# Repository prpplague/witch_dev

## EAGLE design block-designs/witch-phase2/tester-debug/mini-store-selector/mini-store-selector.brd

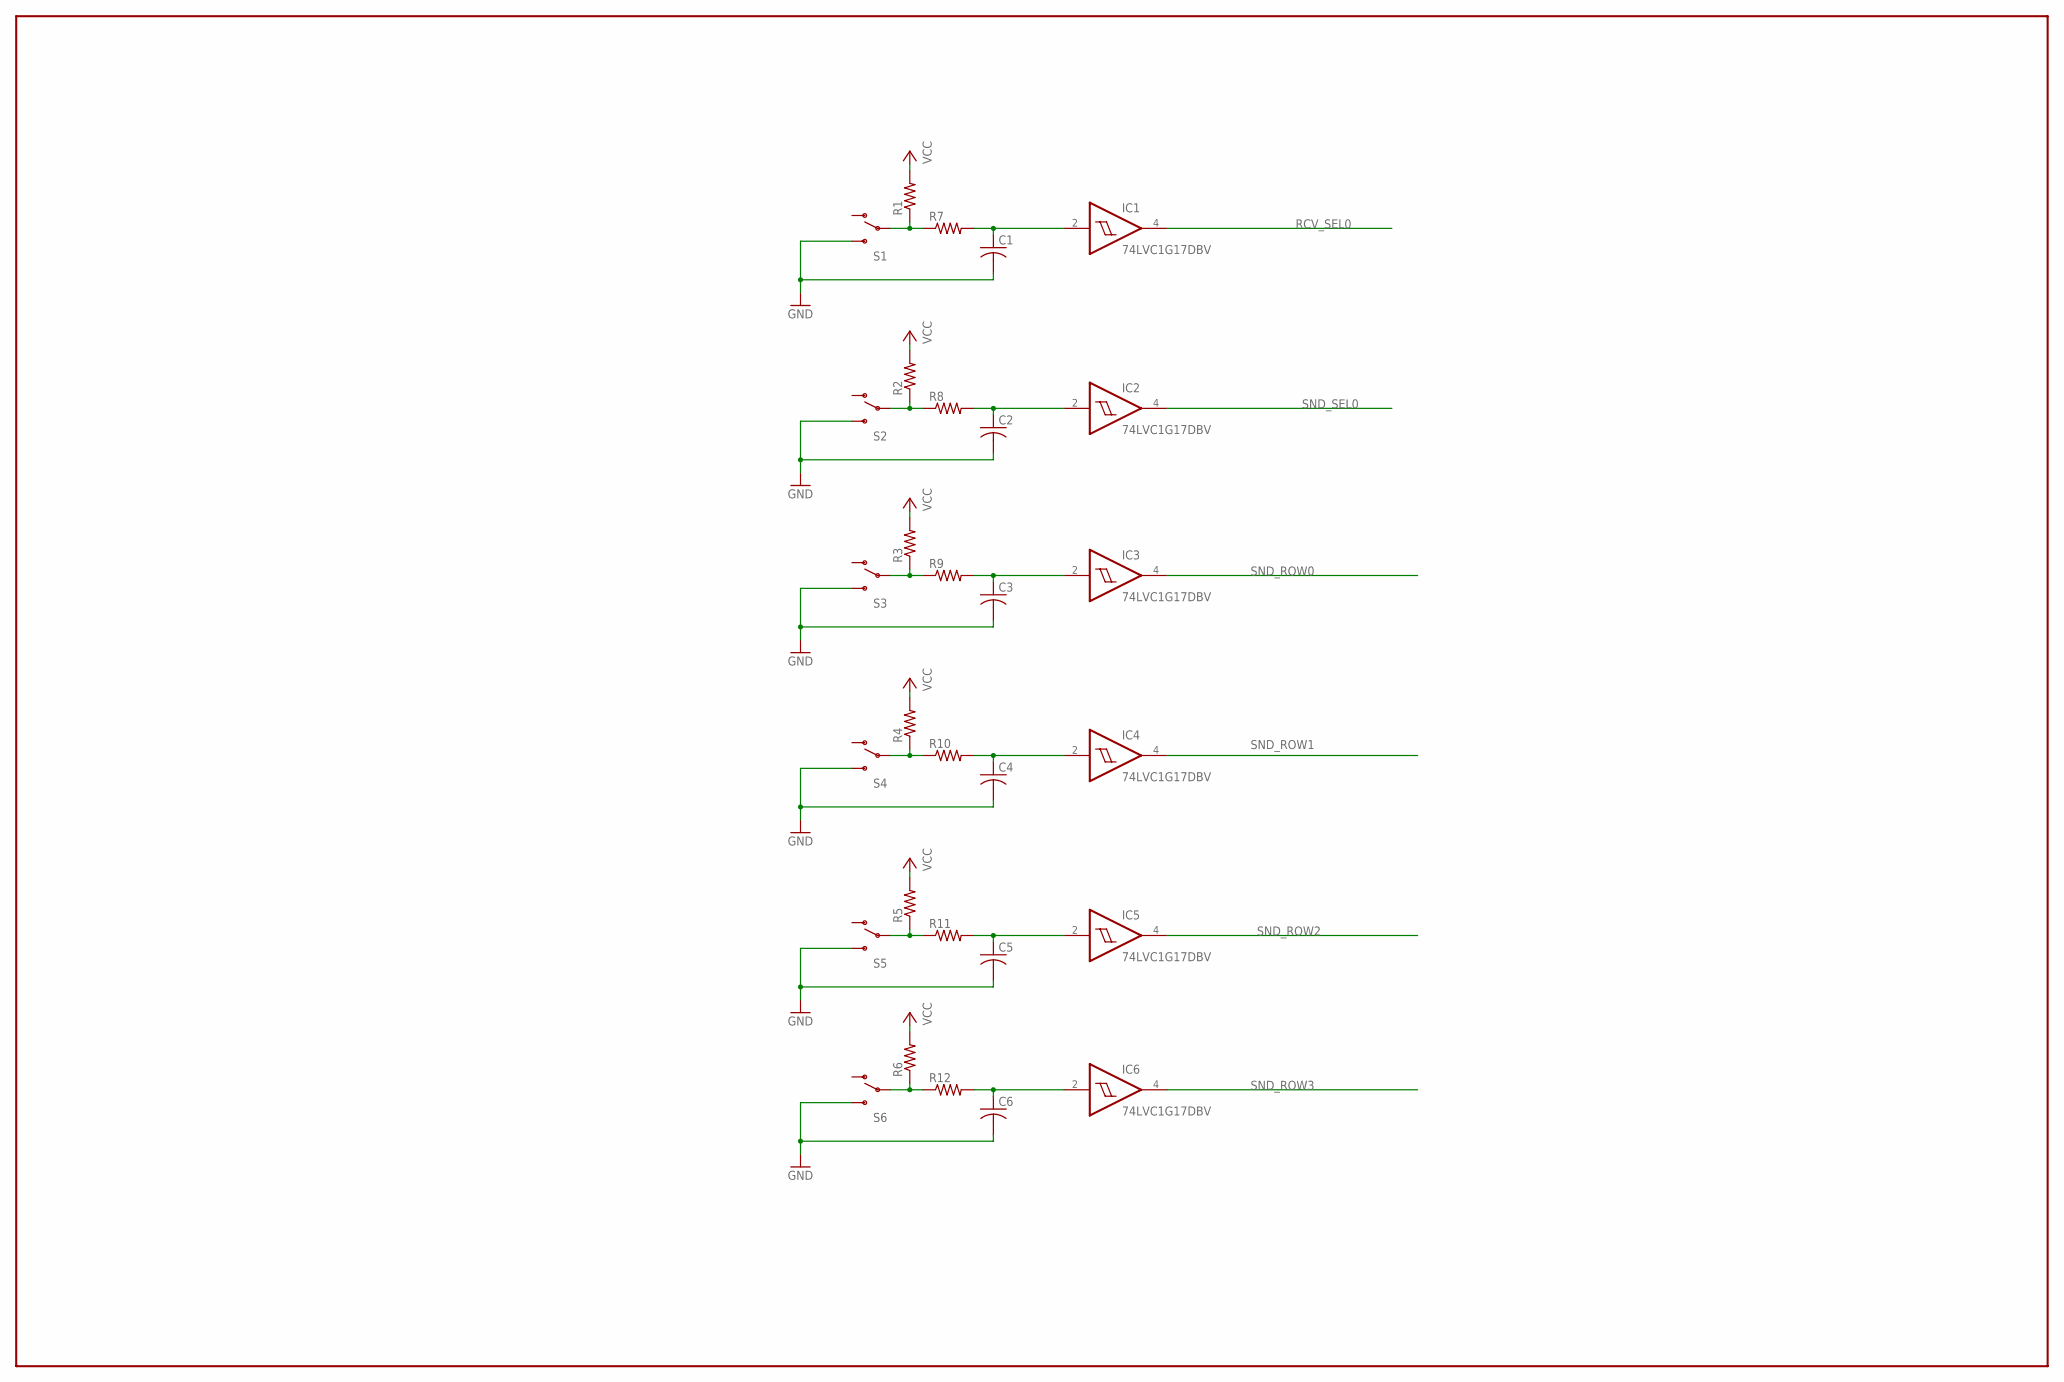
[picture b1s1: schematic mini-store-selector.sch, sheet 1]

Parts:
C1, C2, C3, C4, C5, C6: C-USC0805; C0805
IC1, IC2, IC3, IC4, IC5, IC6: 74LVC1G17DBV; SOT23-5
R1, R2, R3, R4, R5, R6, R7, R8, R9, R10, R11, R12: R-US_R0805; R0805
S1, S2, S3, S4, S5, S6: SWITCH-SPDTPTH; SWITCH-SPDT

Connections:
GND: C1.2, C2.2, C3.2, C4.2, C5.2, C6.2, IC1.3 (GND), IC2.3 (GND), IC3.3 (GND), IC4.3 (GND), IC5.3 (GND), IC6.3 (GND), S1.3 (S), S2.3 (S), S3.3 (S), S4.3 (S), S5.3 (S), S6.3 (S); also elsewhere on the board
unnamed: C6.1, IC6.2 (I), R12.2
unnamed: R6.1, R12.1, S6.2
unnamed: C2.1, IC2.2 (I), R8.2
unnamed: R2.1, R8.1, S2.2
unnamed: C1.1, IC1.2 (I), R7.2
unnamed: C4.1, IC4.2 (I), R10.2
unnamed: R4.1, R10.1, S4.2
unnamed: C3.1, IC3.2 (I), R9.2
unnamed: R3.1, R9.1, S3.2
unnamed: C5.1, IC5.2 (I), R11.2
unnamed: R5.1, R11.1, S5.2
unnamed: R1.1, R7.1, S1.2
RCV_SEL0: IC1.4 (O); also elsewhere on the board
SND_ROW0: IC3.4 (O); also elsewhere on the board
SND_ROW1: IC4.4 (O); also elsewhere on the board
SND_ROW2: IC5.4 (O); also elsewhere on the board
SND_ROW3: IC6.4 (O); also elsewhere on the board
SND_SEL0: IC2.4 (O); also elsewhere on the board
VCC: IC1.5 (VCC), IC2.5 (VCC), IC3.5 (VCC), IC4.5 (VCC), IC5.5 (VCC), IC6.5 (VCC), R1.2, R2.2, R3.2, R4.2, R5.2, R6.2; also elsewhere on the board

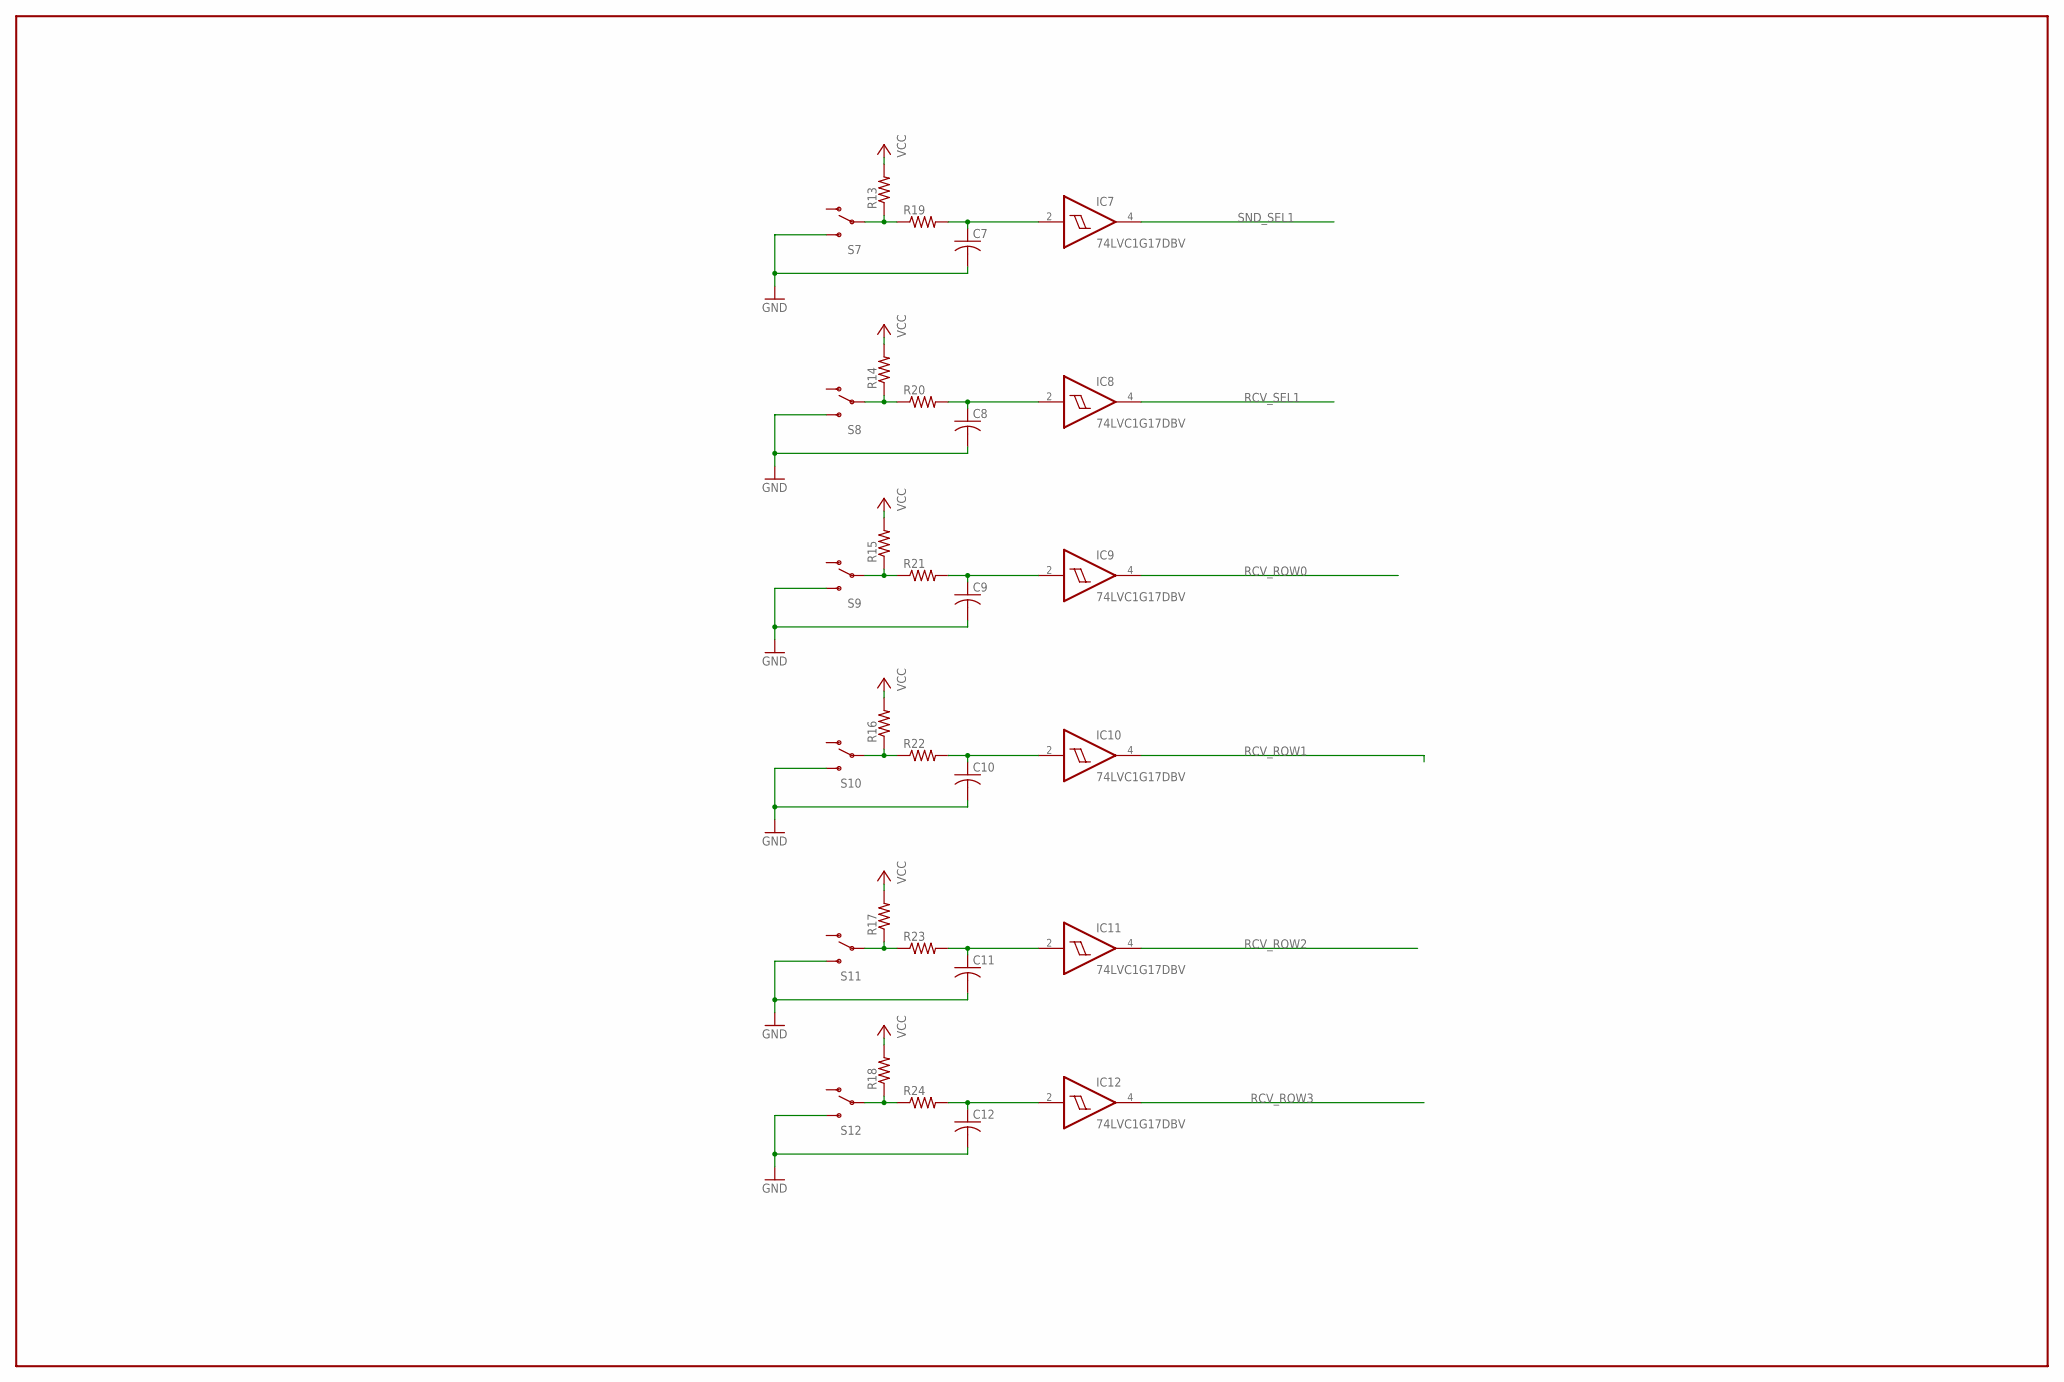
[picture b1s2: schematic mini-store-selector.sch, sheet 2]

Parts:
C7, C8, C9, C10, C11, C12: C-USC0805; C0805
IC7, IC8, IC9, IC10, IC11, IC12: 74LVC1G17DBV; SOT23-5
R13, R14, R15, R16, R17, R18, R19, R20, R21, R22, R23, R24: R-US_R0805; R0805
S7, S8, S9, S10, S11, S12: SWITCH-SPDTPTH; SWITCH-SPDT

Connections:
GND: C7.2, C8.2, C9.2, C10.2, C11.2, C12.2, IC7.3 (GND), IC8.3 (GND), IC9.3 (GND), IC10.3 (GND), IC11.3 (GND), IC12.3 (GND), S7.3 (S), S8.3 (S), S9.3 (S), S10.3 (S), S11.3 (S), S12.3 (S); also elsewhere on the board
unnamed: C10.1, IC10.2 (I), R22.2
unnamed: R16.1, R22.1, S10.2
unnamed: C9.1, IC9.2 (I), R21.2
unnamed: R15.1, R21.1, S9.2
unnamed: C11.1, IC11.2 (I), R23.2
unnamed: R17.1, R23.1, S11.2
unnamed: C12.1, IC12.2 (I), R24.2
unnamed: R18.1, R24.1, S12.2
unnamed: C8.1, IC8.2 (I), R20.2
unnamed: R14.1, R20.1, S8.2
unnamed: C7.1, IC7.2 (I), R19.2
unnamed: R13.1, R19.1, S7.2
RCV_ROW0: IC9.4 (O); also elsewhere on the board
RCV_ROW1: IC10.4 (O); also elsewhere on the board
RCV_ROW2: IC11.4 (O); also elsewhere on the board
RCV_ROW3: IC12.4 (O); also elsewhere on the board
RCV_SEL1: IC8.4 (O); also elsewhere on the board
SND_SEL1: IC7.4 (O); also elsewhere on the board
VCC: IC7.5 (VCC), IC8.5 (VCC), IC9.5 (VCC), IC10.5 (VCC), IC11.5 (VCC), IC12.5 (VCC), R13.2, R14.2, R15.2, R16.2, R17.2, R18.2; also elsewhere on the board

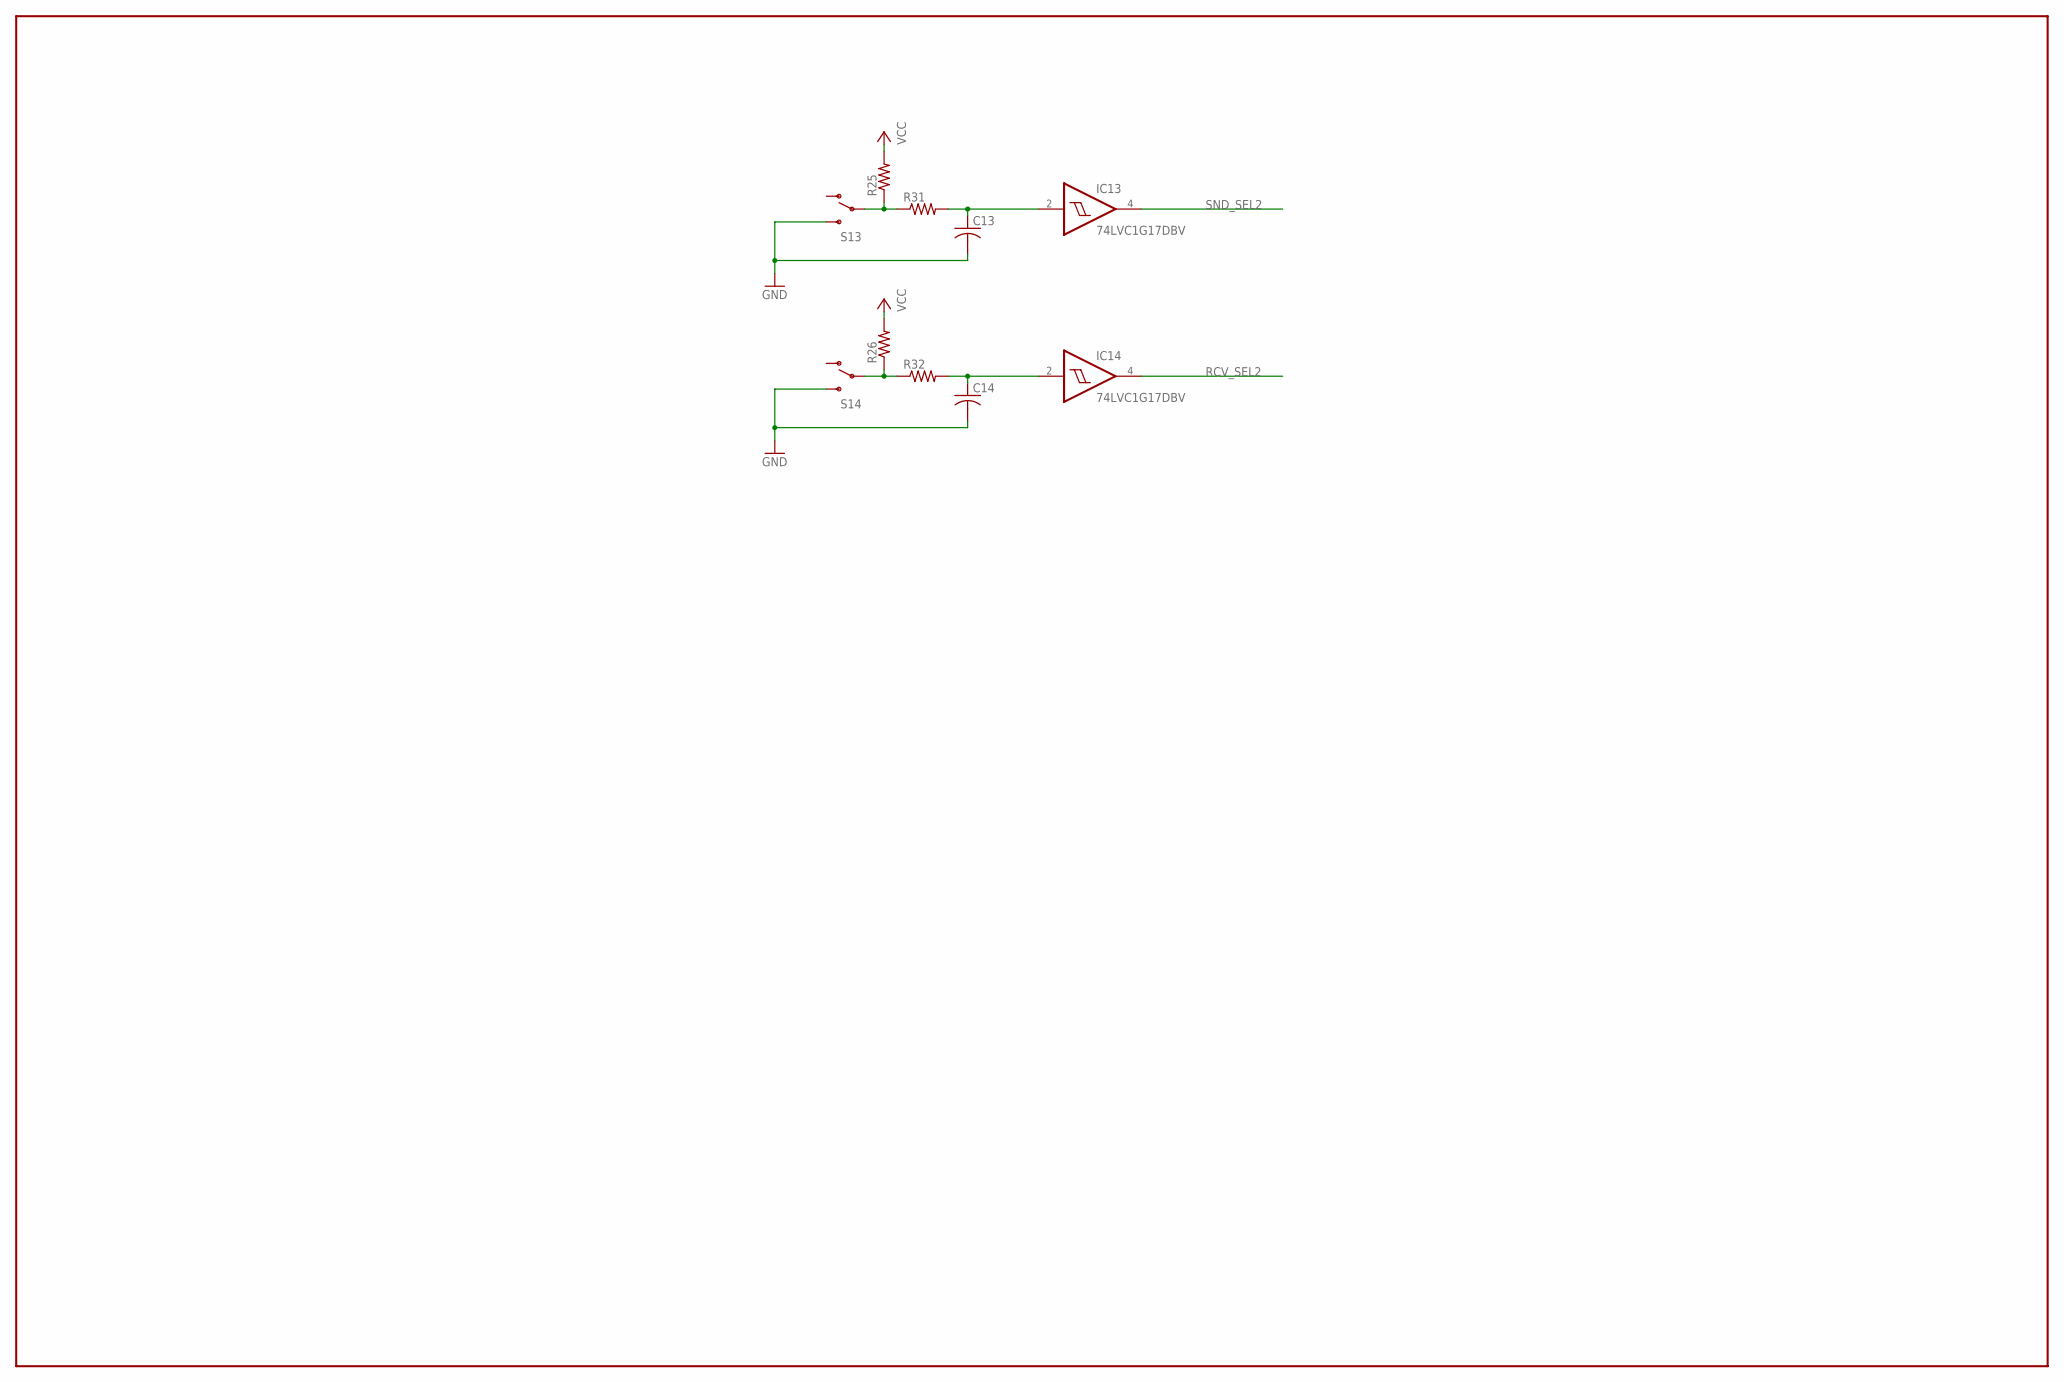
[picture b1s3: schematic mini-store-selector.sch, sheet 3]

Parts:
C13, C14: C-USC0805; C0805
IC13, IC14: 74LVC1G17DBV; SOT23-5
R25, R26, R31, R32: R-US_R0805; R0805
S13, S14: SWITCH-SPDTPTH; SWITCH-SPDT

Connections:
GND: C13.2, C14.2, IC13.3 (GND), IC14.3 (GND), S13.3 (S), S14.3 (S); also elsewhere on the board
unnamed: C14.1, IC14.2 (I), R32.2
unnamed: R26.1, R32.1, S14.2
unnamed: C13.1, IC13.2 (I), R31.2
unnamed: R25.1, R31.1, S13.2
RCV_SEL2: IC14.4 (O); also elsewhere on the board
SND_SEL2: IC13.4 (O); also elsewhere on the board
VCC: IC13.5 (VCC), IC14.5 (VCC), R25.2, R26.2; also elsewhere on the board

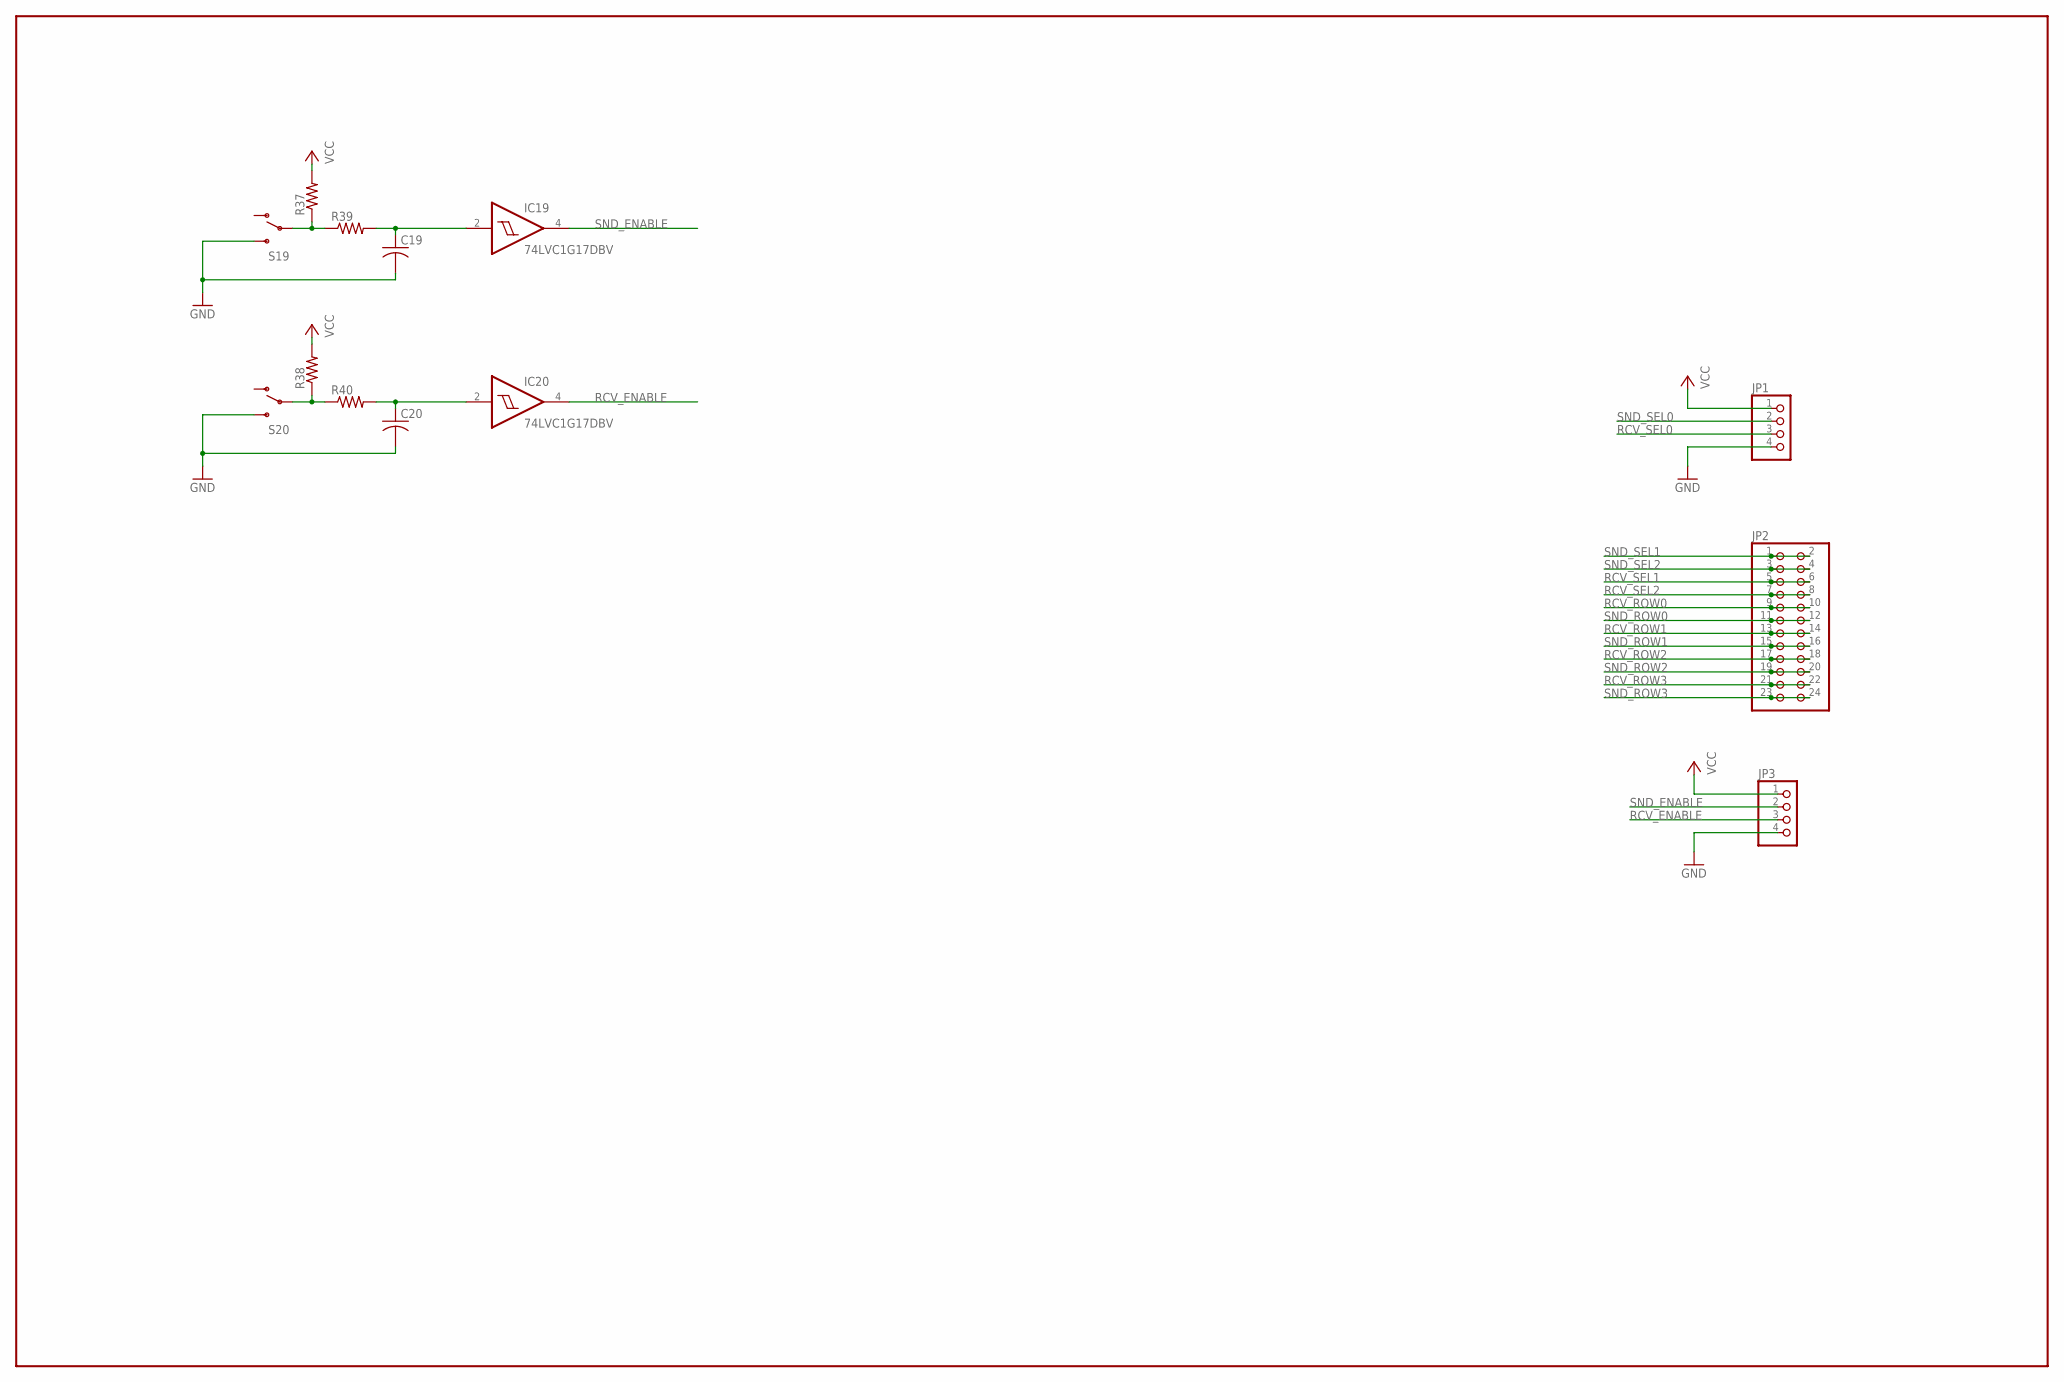
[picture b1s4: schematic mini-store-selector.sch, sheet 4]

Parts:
C19, C20: C-USC0805; C0805
IC19, IC20: 74LVC1G17DBV; SOT23-5
JP1, JP3: PINHD-1X4; 1X04
JP2: PINHD-2X12; 2X12
R37, R38, R39, R40: R-US_R0805; R0805
S19, S20: SWITCH-SPDTPTH; SWITCH-SPDT

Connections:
GND: C19.2, C20.2, IC19.3 (GND), IC20.3 (GND), JP1.4, JP3.4, S19.3 (S), S20.3 (S); also elsewhere on the board
unnamed: C20.1, IC20.2 (I), R40.2
unnamed: R38.1, R40.1, S20.2
unnamed: C19.1, IC19.2 (I), R39.2
unnamed: R37.1, R39.1, S19.2
RCV_ENABLE: IC20.4 (O), JP3.3
RCV_ROW0: JP2.9, JP2.10; also elsewhere on the board
RCV_ROW1: JP2.13, JP2.14; also elsewhere on the board
RCV_ROW2: JP2.17, JP2.18; also elsewhere on the board
RCV_ROW3: JP2.21, JP2.22; also elsewhere on the board
RCV_SEL0: JP1.3; also elsewhere on the board
RCV_SEL1: JP2.5, JP2.6; also elsewhere on the board
RCV_SEL2: JP2.7, JP2.8; also elsewhere on the board
SND_ENABLE: IC19.4 (O), JP3.2
SND_ROW0: JP2.11, JP2.12; also elsewhere on the board
SND_ROW1: JP2.15, JP2.16; also elsewhere on the board
SND_ROW2: JP2.19, JP2.20; also elsewhere on the board
SND_ROW3: JP2.23, JP2.24; also elsewhere on the board
SND_SEL0: JP1.2; also elsewhere on the board
SND_SEL1: JP2.1, JP2.2; also elsewhere on the board
SND_SEL2: JP2.3, JP2.4; also elsewhere on the board
VCC: IC19.5 (VCC), IC20.5 (VCC), JP1.1, JP3.1, R37.2, R38.2; also elsewhere on the board

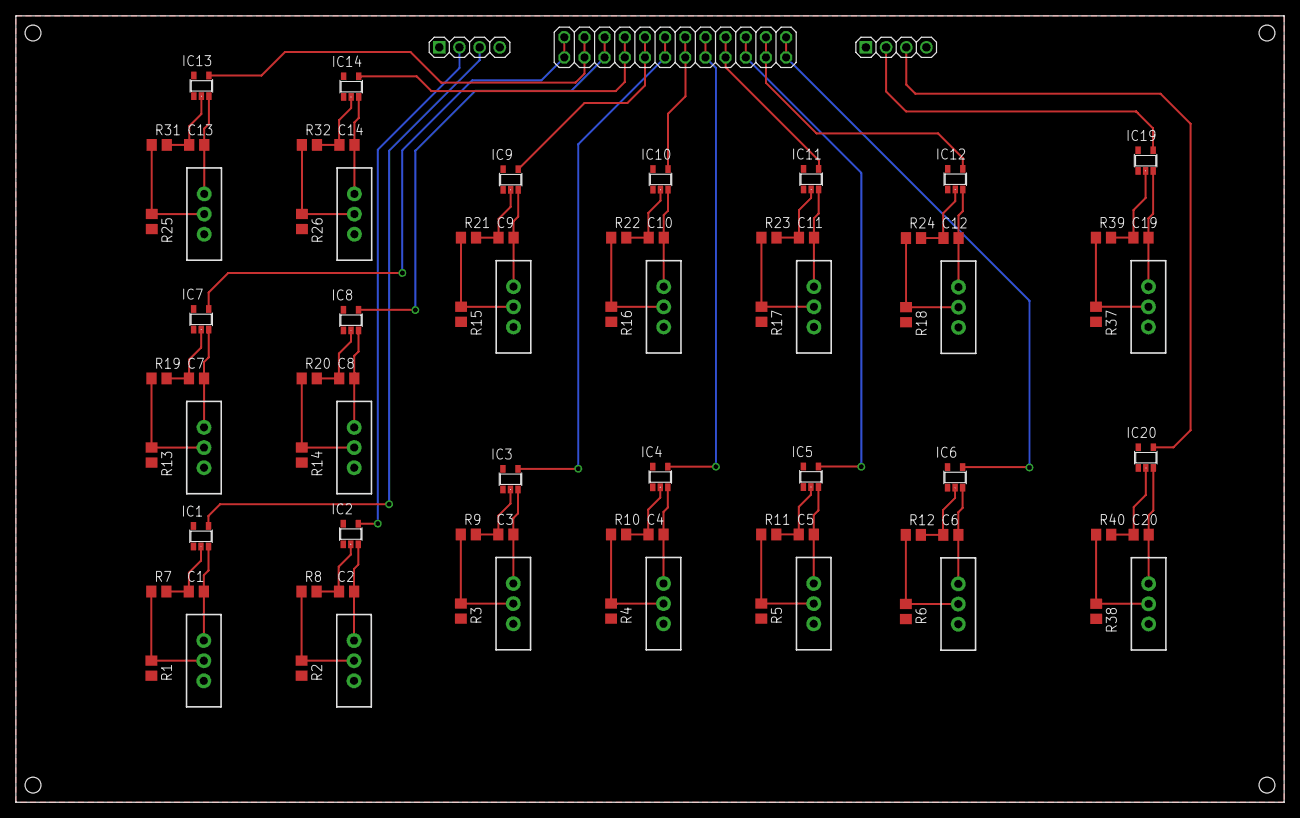
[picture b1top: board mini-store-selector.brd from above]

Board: 2 copper layers, 159.8 x 99.1 mm, 83 parts (0 on the bottom side), 50 nets.

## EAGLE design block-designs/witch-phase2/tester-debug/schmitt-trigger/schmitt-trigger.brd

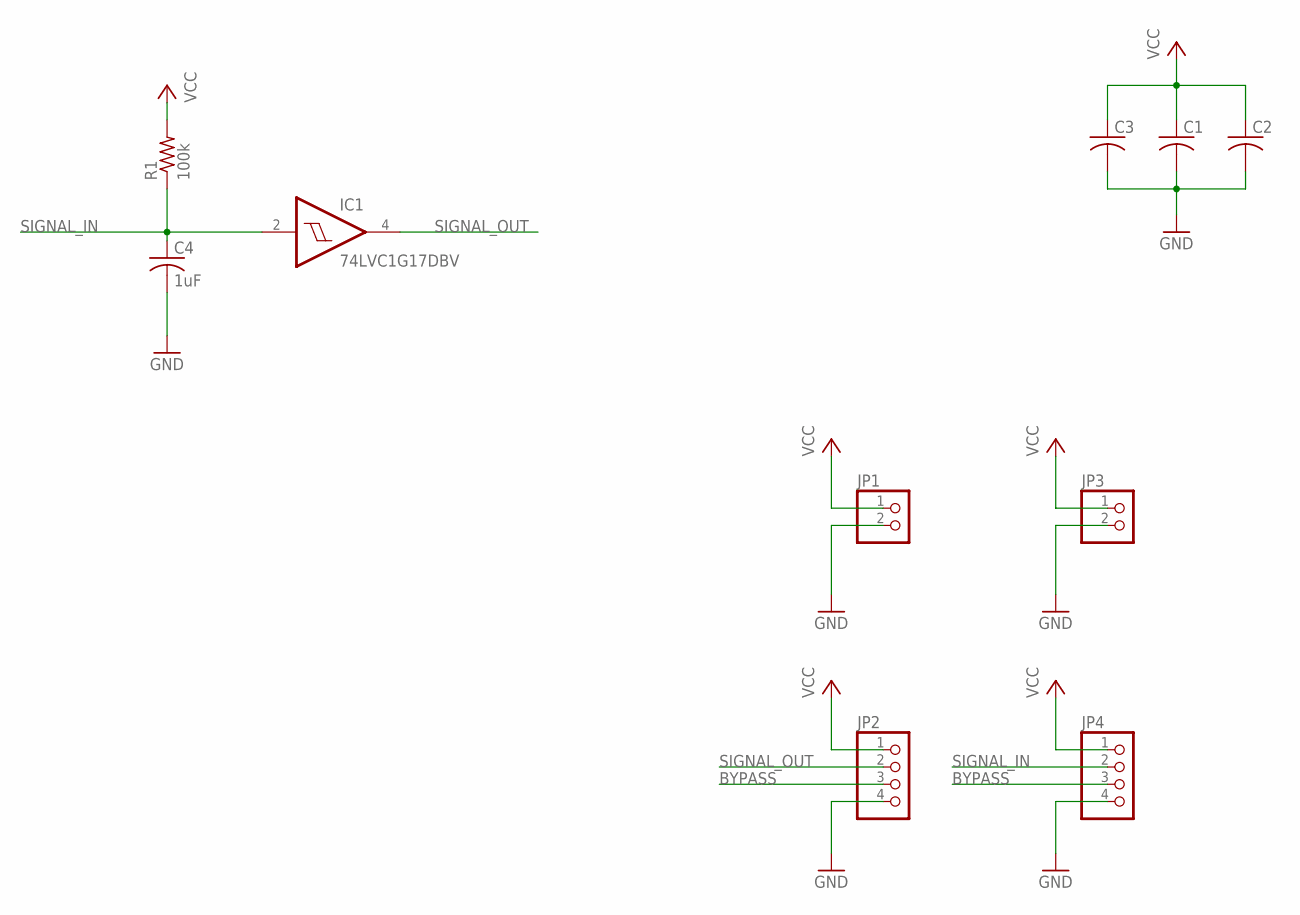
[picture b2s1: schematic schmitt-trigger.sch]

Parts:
C1, C2, C3: C-USC0603K; C0603K
C4: 1uF; C0603K
IC1: 74LVC1G17DBV; SOT23-5
JP1, JP3: PINHD-1X2; 1X02
JP2, JP4: PINHD-1X4; 1X04
R1: 100k; R0603

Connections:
BYPASS: JP2.3, JP4.3
GND: C1.2, C2.2, C3.2, C4.2, IC1.3 (GND), JP1.2, JP2.4, JP3.2, JP4.4
SIGNAL_IN: C4.1, IC1.2 (I), JP4.2, R1.1
SIGNAL_OUT: IC1.4 (O), JP2.2
VCC: C1.1, C2.1, C3.1, IC1.5 (VCC), JP1.1, JP2.1, JP3.1, JP4.1, R1.2

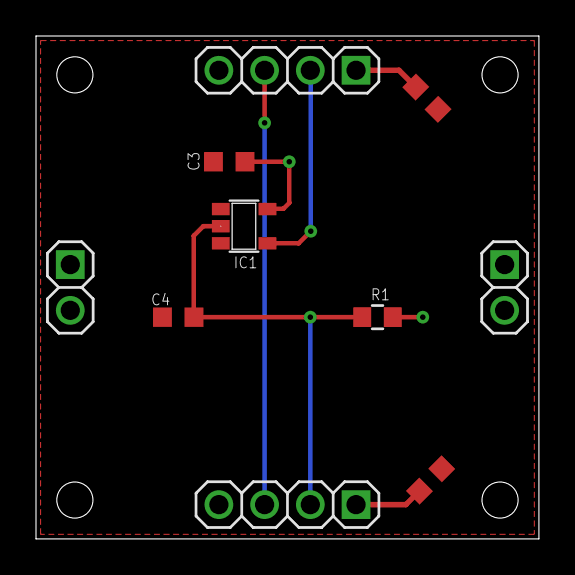
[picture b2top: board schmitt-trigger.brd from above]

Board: 2 copper layers, 27.9 x 27.9 mm, 10 parts (0 on the bottom side), 5 nets.

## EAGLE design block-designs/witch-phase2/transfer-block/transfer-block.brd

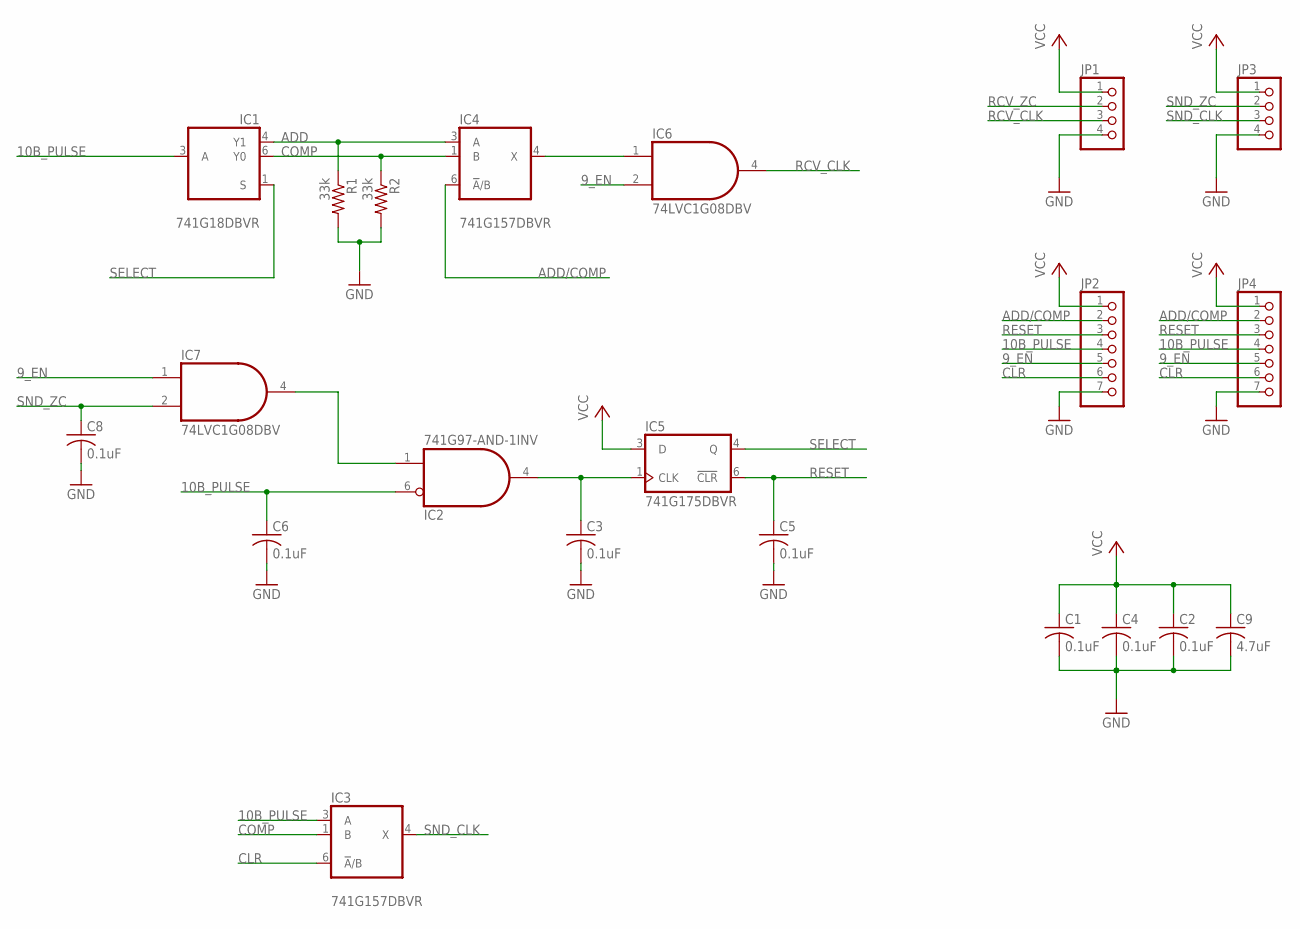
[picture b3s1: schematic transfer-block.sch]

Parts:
C1, C2, C3, C4, C5, C6, C8: 0.1uF; C0603K
C9: 4.7uF; C0603K
IC1: 741G18DBVR; DBV_R-PDSO-G6
IC2: 741G97-AND-1INV; DBV_R-PDSO-G6
IC3, IC4: 741G157DBVR; DBV_R-PDSO-G6
IC5: 741G175DBVR; DBV_R-PDSO-G6
IC6, IC7: 74LVC1G08DBV; SOT23-5
JP1, JP3: PINHD-1X4; 1X04
JP2, JP4: PINHD-1X7; 1X07
R1, R2: 33k; R0603

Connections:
9_EN: IC6.2 (I1), IC7.1 (I0), JP2.5, JP4.5
10B_PULSE: C6.1, IC1.3 (A), IC2.6 (I0), IC3.3 (A), JP2.4, JP4.4
ADD: IC1.4 (Y1), IC4.3 (A), R1.1
ADD/COMP: IC4.6 (!A!/B), JP2.2, JP4.2
CLR: IC3.6 (!A!/B), JP2.6, JP4.6
COMP: IC1.6 (Y0), IC3.1 (B), IC4.1 (B), R2.1
GND: C1.2, C2.2, C3.2, C4.2, C5.2, C6.2, C8.2, C9.2, IC1.2 (GND), IC2.2 (GND), IC2.3 (GND), IC3.2 (GND), IC4.2 (GND), IC5.2 (GND), IC6.3 (GND), IC7.3 (GND), JP1.4, JP2.7, JP3.4, JP4.7, R1.2, R2.2
unnamed: IC2.1 (I1), IC7.4 (O)
PRE_RCV_CLK: IC4.4 (X), IC6.1 (I0)
RCV_CLK: IC6.4 (O), JP1.3
RCV_ZC: JP1.2
RESET: C5.1, IC5.6 (!CLR), JP2.3, JP4.3
SELECT: IC1.1 (S), IC5.4 (Q)
SND_CLK: IC3.4 (X), JP3.3
SND_ZC: C8.1, IC7.2 (I1), JP3.2
VCC: C1.1, C2.1, C4.1, C9.1, IC1.5 (VCC), IC2.5 (VCC), IC3.5 (VCC), IC4.5 (VCC), IC5.3 (D), IC5.5 (VCC), IC6.5 (VCC), IC7.5 (VCC), JP1.1, JP2.1, JP3.1, JP4.1
ZC_EN: C3.1, IC2.4 (O), IC5.1 (CLK)

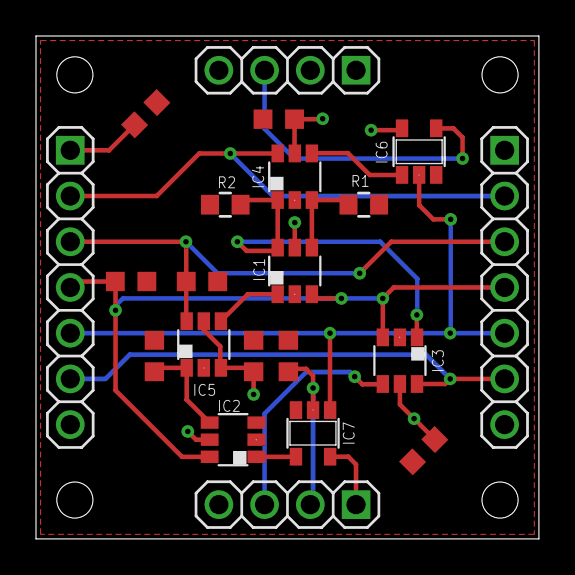
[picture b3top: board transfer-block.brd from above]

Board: 2 copper layers, 27.9 x 27.9 mm, 21 parts (0 on the bottom side), 16 nets.

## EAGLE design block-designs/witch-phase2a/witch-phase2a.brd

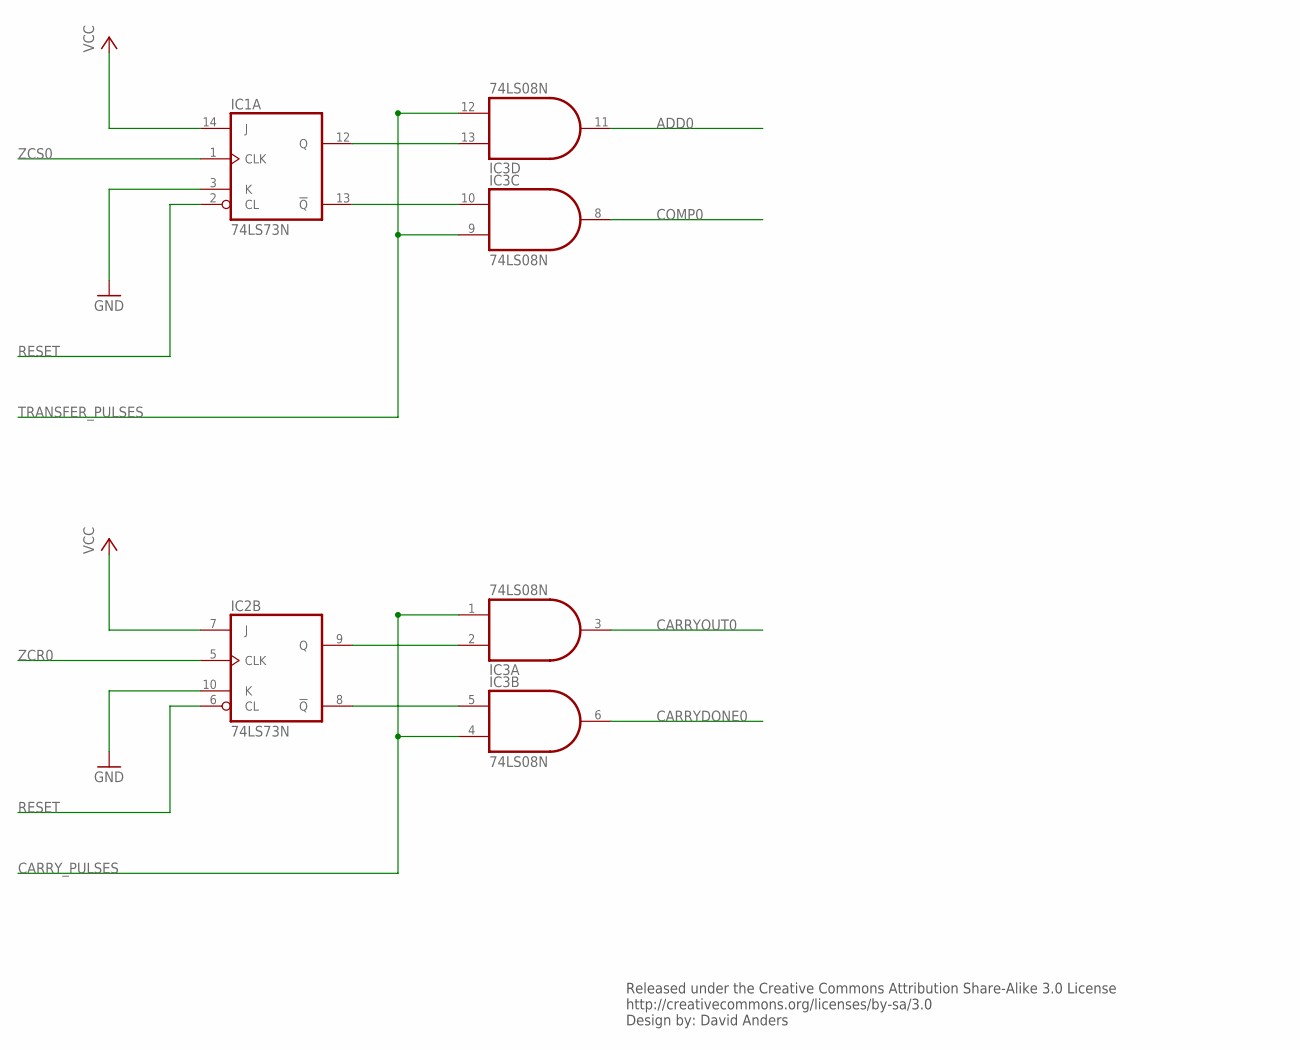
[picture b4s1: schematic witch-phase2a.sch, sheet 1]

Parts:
IC1, IC2: 74LS73N; DIL14
IC3: 74LS08N; DIL14

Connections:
ADD0: IC3.11 (O); also elsewhere on the board
CARRYDONE0: IC3.6 (O); also elsewhere on the board
CARRYOUT0: IC3.3 (O); also elsewhere on the board
CARRY_PULSES: IC3.1 (I0), IC3.4 (I0); also elsewhere on the board
COMP0: IC3.8 (O); also elsewhere on the board
GND: IC1.3 (K), IC2.10 (K); also elsewhere on the board
unnamed: IC2.9 (Q), IC3.2 (I1)
unnamed: IC2.8 (!Q), IC3.5 (I1)
unnamed: IC1.12 (Q), IC3.13 (I1)
unnamed: IC1.13 (!Q), IC3.10 (I1)
RESET: IC1.2 (CL), IC2.6 (CL); also elsewhere on the board
TRANSFER_PULSES: IC3.9 (I0), IC3.12 (I0); also elsewhere on the board
VCC: IC1.14 (J), IC2.7 (J); also elsewhere on the board
ZCR0: IC2.5 (CLK); also elsewhere on the board
ZCS0: IC1.1 (CLK); also elsewhere on the board

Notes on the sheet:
Released under the Creative Commons Attribution Share-Alike 3.0 License http://creativecommons.org/licenses/by-sa/3.0 Design by: David Anders

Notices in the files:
parts and their libraries:
SparkFun-Electromechanical: Licensing: CC v3.0 Share-Alike You are welcome to use this library for commercial purposes.
SparkFun-Connectors: Licensing: Creative Commons ShareAlike 4.0 International - https://creativecommons.org/licenses/by-sa/4.0
